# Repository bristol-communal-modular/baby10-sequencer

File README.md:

# Baby 10 Sequencer

A KiCAD project for the Baby 10 sequencer

## Contact

Drop me an email at guy@rumblesan.com

## License

This work is licensed under a [Creative Commons Attribution 4.0 International License]("http://creativecommons.org/licenses/by/4.0/")

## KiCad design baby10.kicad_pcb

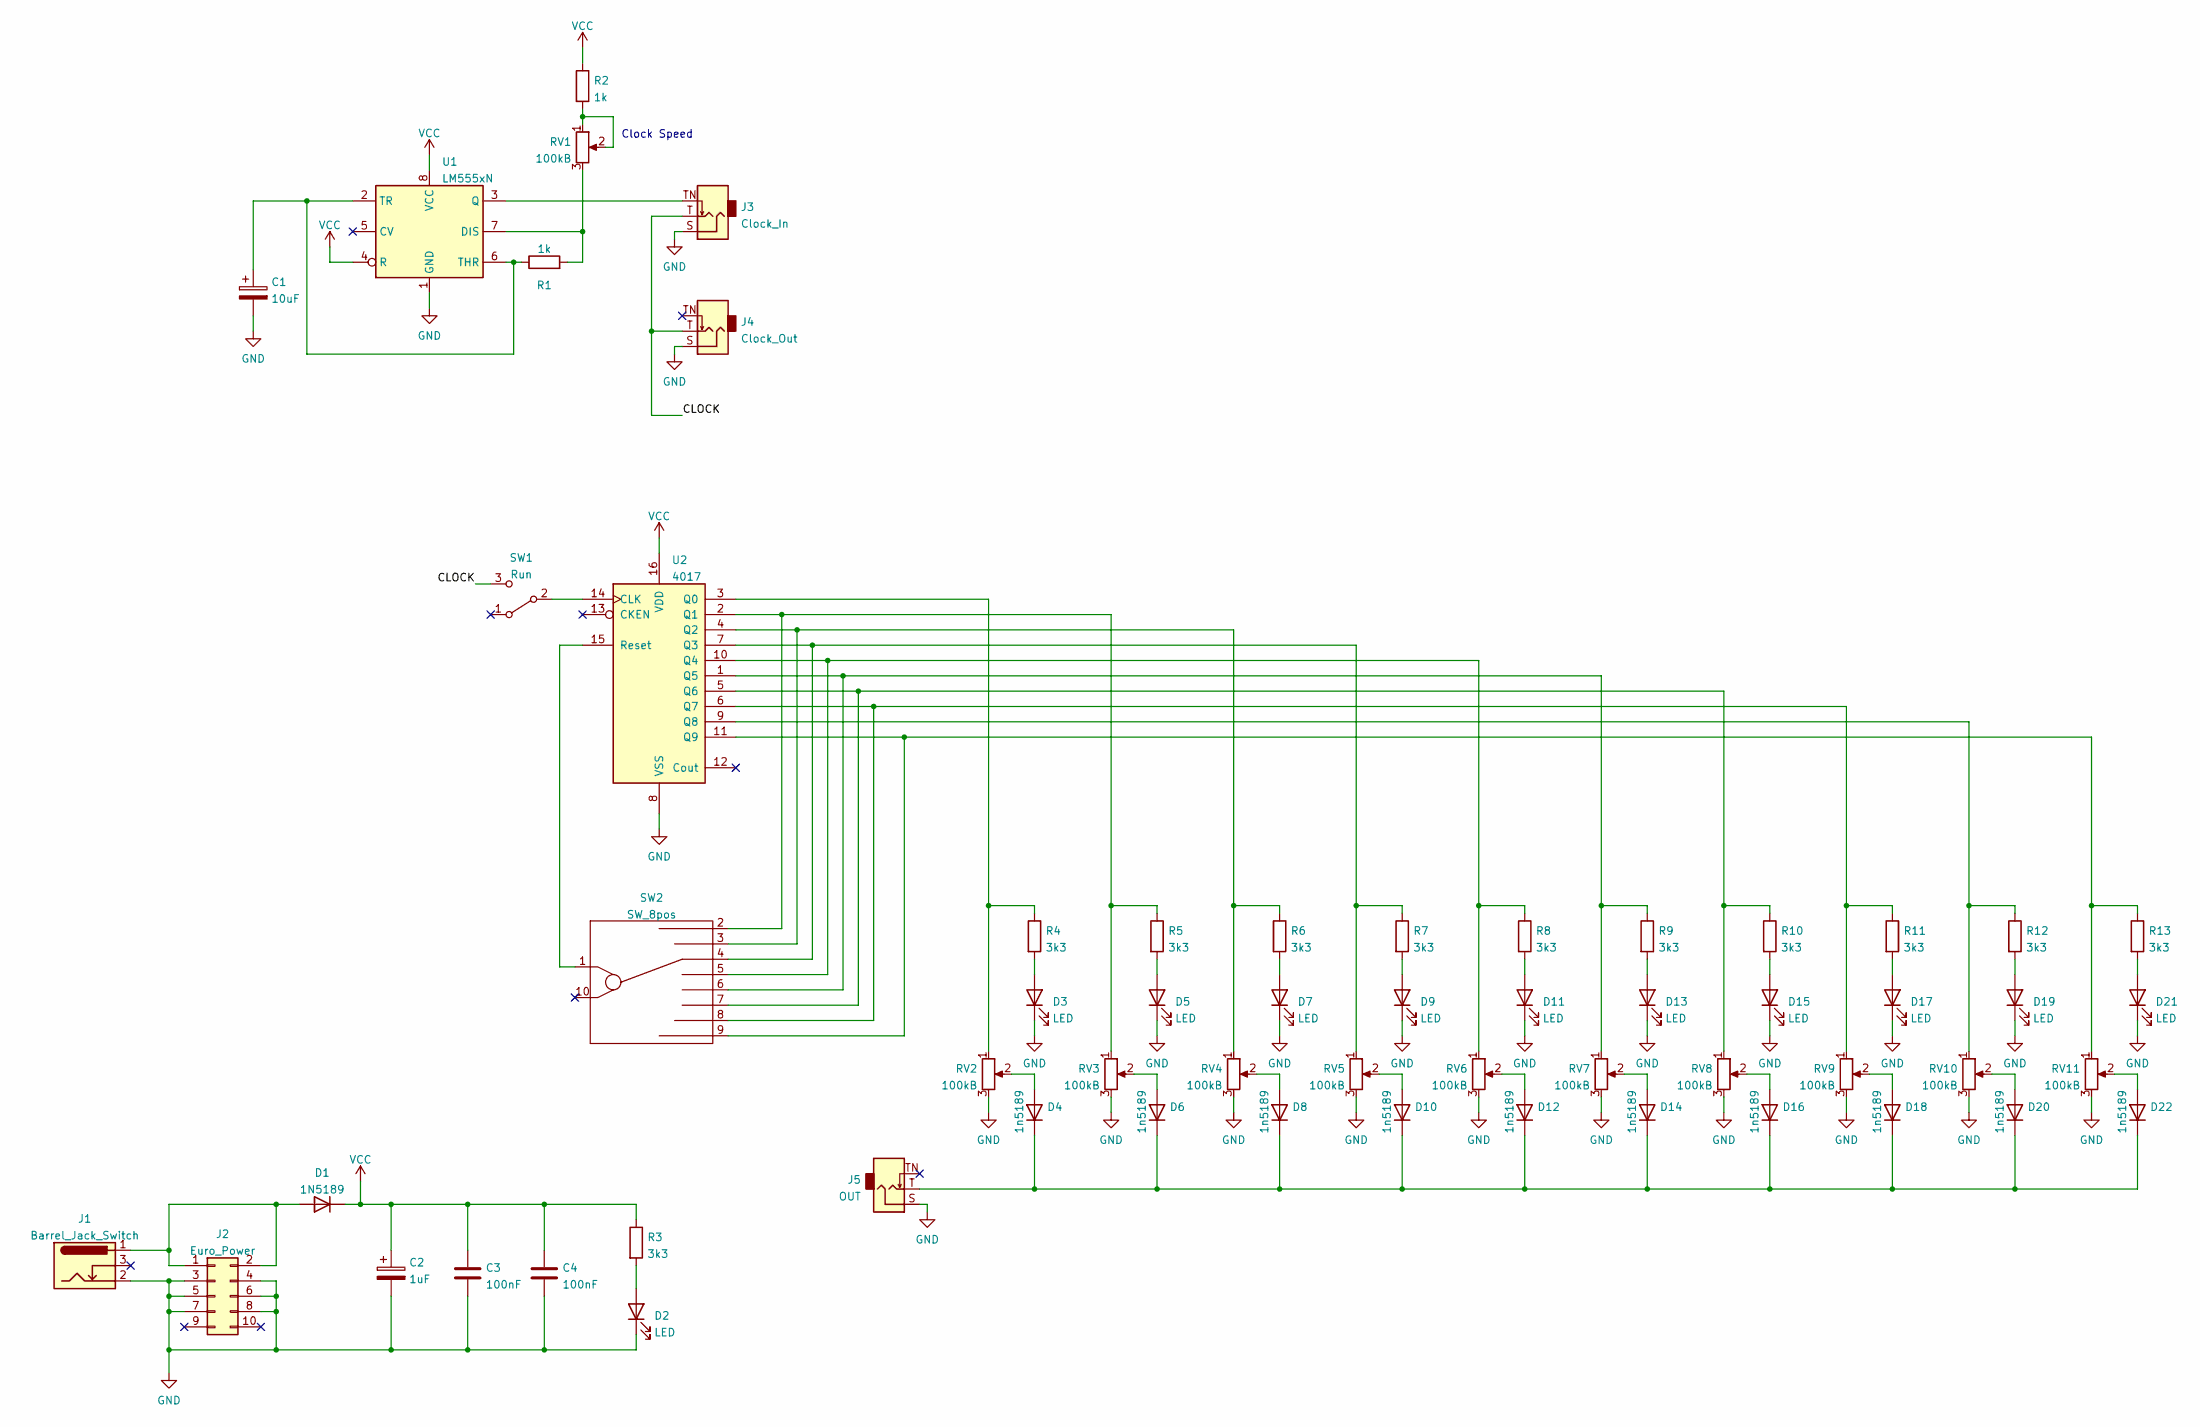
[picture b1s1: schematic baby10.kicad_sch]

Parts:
C1: 10uF; CP_Radial_D5.0mm_P2.50mm
C2: 1uF; CP_Radial_D5.0mm_P2.50mm
C3, C4: 100nF; C_Rect_L7.0mm_W3.5mm_P2.50mm_P5.00mm
D1: 1N5189; D_DO-35_SOD27_P7.62mm_Horizontal
D2, D3, D5, D7, D9, D11, D13, D15, D17, D19, D21: LED; LED_D5.0mm
D4, D6, D8, D10, D12, D14, D16, D18, D20, D22: 1n5189; D_DO-35_SOD27_P7.62mm_Horizontal
J1: Barrel_Jack_Switch; BarrelJack_CUI_PJ-102AH_Horizontal
J2: Euro_Power; PinSocket_2x05_P2.54mm_Vertical
J3: Clock_In; Jack_3.5mm_QingPu_WQP-PJ398SM_Vertical
J4: Clock_Out; Jack_3.5mm_QingPu_WQP-PJ398SM_Vertical
J5: OUT; Jack_3.5mm_QingPu_WQP-PJ398SM_Vertical
R1, R2: 1k; R_Axial_DIN0207_L6.3mm_D2.5mm_P7.62mm_Horizontal
R3, R4, R5, R6, R7, R8, R9, R10, R11, R12, R13: 3k3; R_Axial_DIN0207_L6.3mm_D2.5mm_P7.62mm_Horizontal
RV1, RV2, RV3, RV4, RV5, RV6, RV7, RV8, RV9, RV10, RV11: 100kB; Potentiometer_Alpha_RD901F-40-00D_Single_Vertical_CircularH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
SW1: Run; SW_SPDT_DailyWell_MiniToggle
SW2: SW_8pos; alpha_rotary_8
U1: LM555xN; DIP-8_W7.62mm
U2: 4017; DIP-16_W7.62mm

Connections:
/CLOCK: J3.T, J4.T, SW1.3 (C)
GND: C1.2, C2.2, C3.2, C4.2, D2.1 (K), D3.1 (K), D5.1 (K), D7.1 (K), D9.1 (K), D11.1 (K), D13.1 (K), D15.1 (K), D17.1 (K), D19.1 (K), D21.1 (K), J1.2, J2.3, J2.4, J2.5, J2.6, J2.7, J2.8, J3.S, J4.S, J5.S, RV2.3, RV3.3, RV4.3, RV5.3, RV6.3, RV7.3, RV8.3, RV9.3, RV10.3, RV11.3, U1.1 (GND), U2.8 (VSS)
unnamed: C1.1, R1.1, U1.2 (TR), U1.6 (THR)
unnamed: D1.2 (A), J1.1, J2.1, J2.2
unnamed: D2.2 (A), R3.2
unnamed: D3.2 (A), R4.2
unnamed: D4.2 (A), RV2.2
unnamed: D5.2 (A), R5.2
unnamed: D6.2 (A), RV3.2
unnamed: D7.2 (A), R6.2
unnamed: D8.2 (A), RV4.2
unnamed: D9.2 (A), R7.2
unnamed: D4.1 (K), D6.1 (K), D8.1 (K), D10.1 (K), D12.1 (K), D14.1 (K), D16.1 (K), D18.1 (K), D20.1 (K), D22.1 (K), J5.T
unnamed: D10.2 (A), RV5.2
unnamed: D11.2 (A), R8.2
unnamed: D12.2 (A), RV6.2
unnamed: D13.2 (A), R9.2
unnamed: D14.2 (A), RV7.2
unnamed: D15.2 (A), R10.2
unnamed: D16.2 (A), RV8.2
unnamed: D17.2 (A), R11.2
unnamed: D18.2 (A), RV9.2
unnamed: D19.2 (A), R12.2
unnamed: D20.2 (A), RV10.2
unnamed: D21.2 (A), R13.2
unnamed: D22.2 (A), RV11.2
unnamed: J3.TN, U1.3 (Q)
unnamed: R1.2, RV1.3, U1.7 (DIS)
unnamed: R2.2, RV1.1, RV1.2
unnamed: R4.1, RV2.1, U2.3 (Q0)
unnamed: R5.1, RV3.1, SW2.2, U2.2 (Q1)
unnamed: R6.1, RV4.1, SW2.3, U2.4 (Q2)
unnamed: R7.1, RV5.1, SW2.4, U2.7 (Q3)
unnamed: R8.1, RV6.1, SW2.5, U2.10 (Q4)
unnamed: R9.1, RV7.1, SW2.6, U2.1 (Q5)
unnamed: R10.1, RV8.1, SW2.7, U2.5 (Q6)
unnamed: R11.1, RV9.1, SW2.8, U2.6 (Q7)
unnamed: R12.1, RV10.1, U2.9 (Q8)
unnamed: R13.1, RV11.1, SW2.9, U2.11 (Q9)
unnamed: SW1.2 (B), U2.14 (CLK)
unnamed: SW2.1, U2.15 (Reset)
VCC: C2.1, C3.1, C4.1, D1.1 (K), R2.1, R3.1, U1.4 (R), U1.8 (VCC), U2.16 (VDD)

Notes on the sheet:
Clock Speed

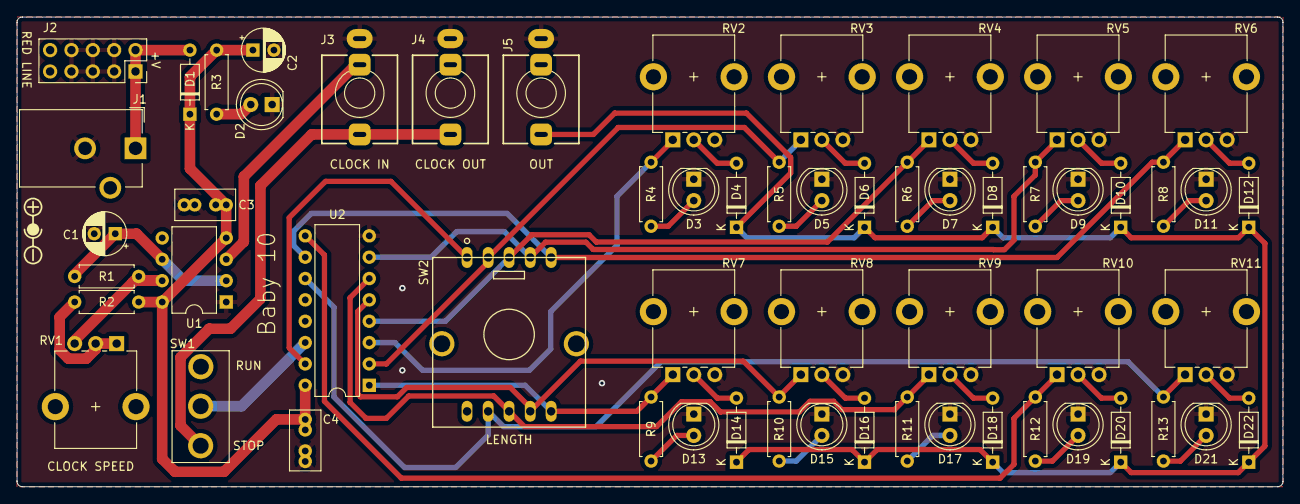
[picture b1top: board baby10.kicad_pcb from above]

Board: 2 copper layers, 150.6 x 55.9 mm, 59 parts (0 on the bottom side), 42 nets.

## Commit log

2022-04-22 Change diodes
2022-04-22 Adding readme
